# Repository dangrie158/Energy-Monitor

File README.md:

# Energy Monitor

A simple 6-channel  energy monitor for the whole house.
Uses 0-5V Current Transducers for current measureent and has a build-in voltage transformer for voltage measurement.
Brains are a Raspberry Pi Zero due to low cost and easy integration into the home WiFi and inclusion with MQTT or any other protocol to include the measurements in all kinds of home automation systems.

## Example Configuration

Channels 1, 2, 3 on L1, L2, L3 -> whole house consumption
Channels 4, 5, 6 on different room connections / devices

## Known Limitations

The Voltage is only measured on a single phase and thus only apperant power can be measured on the channels that connect to a different phase than the supply phase

## Licence

<p xmlns:dct="http://purl.org/dc/terms/" xmlns:vcard="http://www.w3.org/2001/vcard-rdf/3.0#">
  
</p>

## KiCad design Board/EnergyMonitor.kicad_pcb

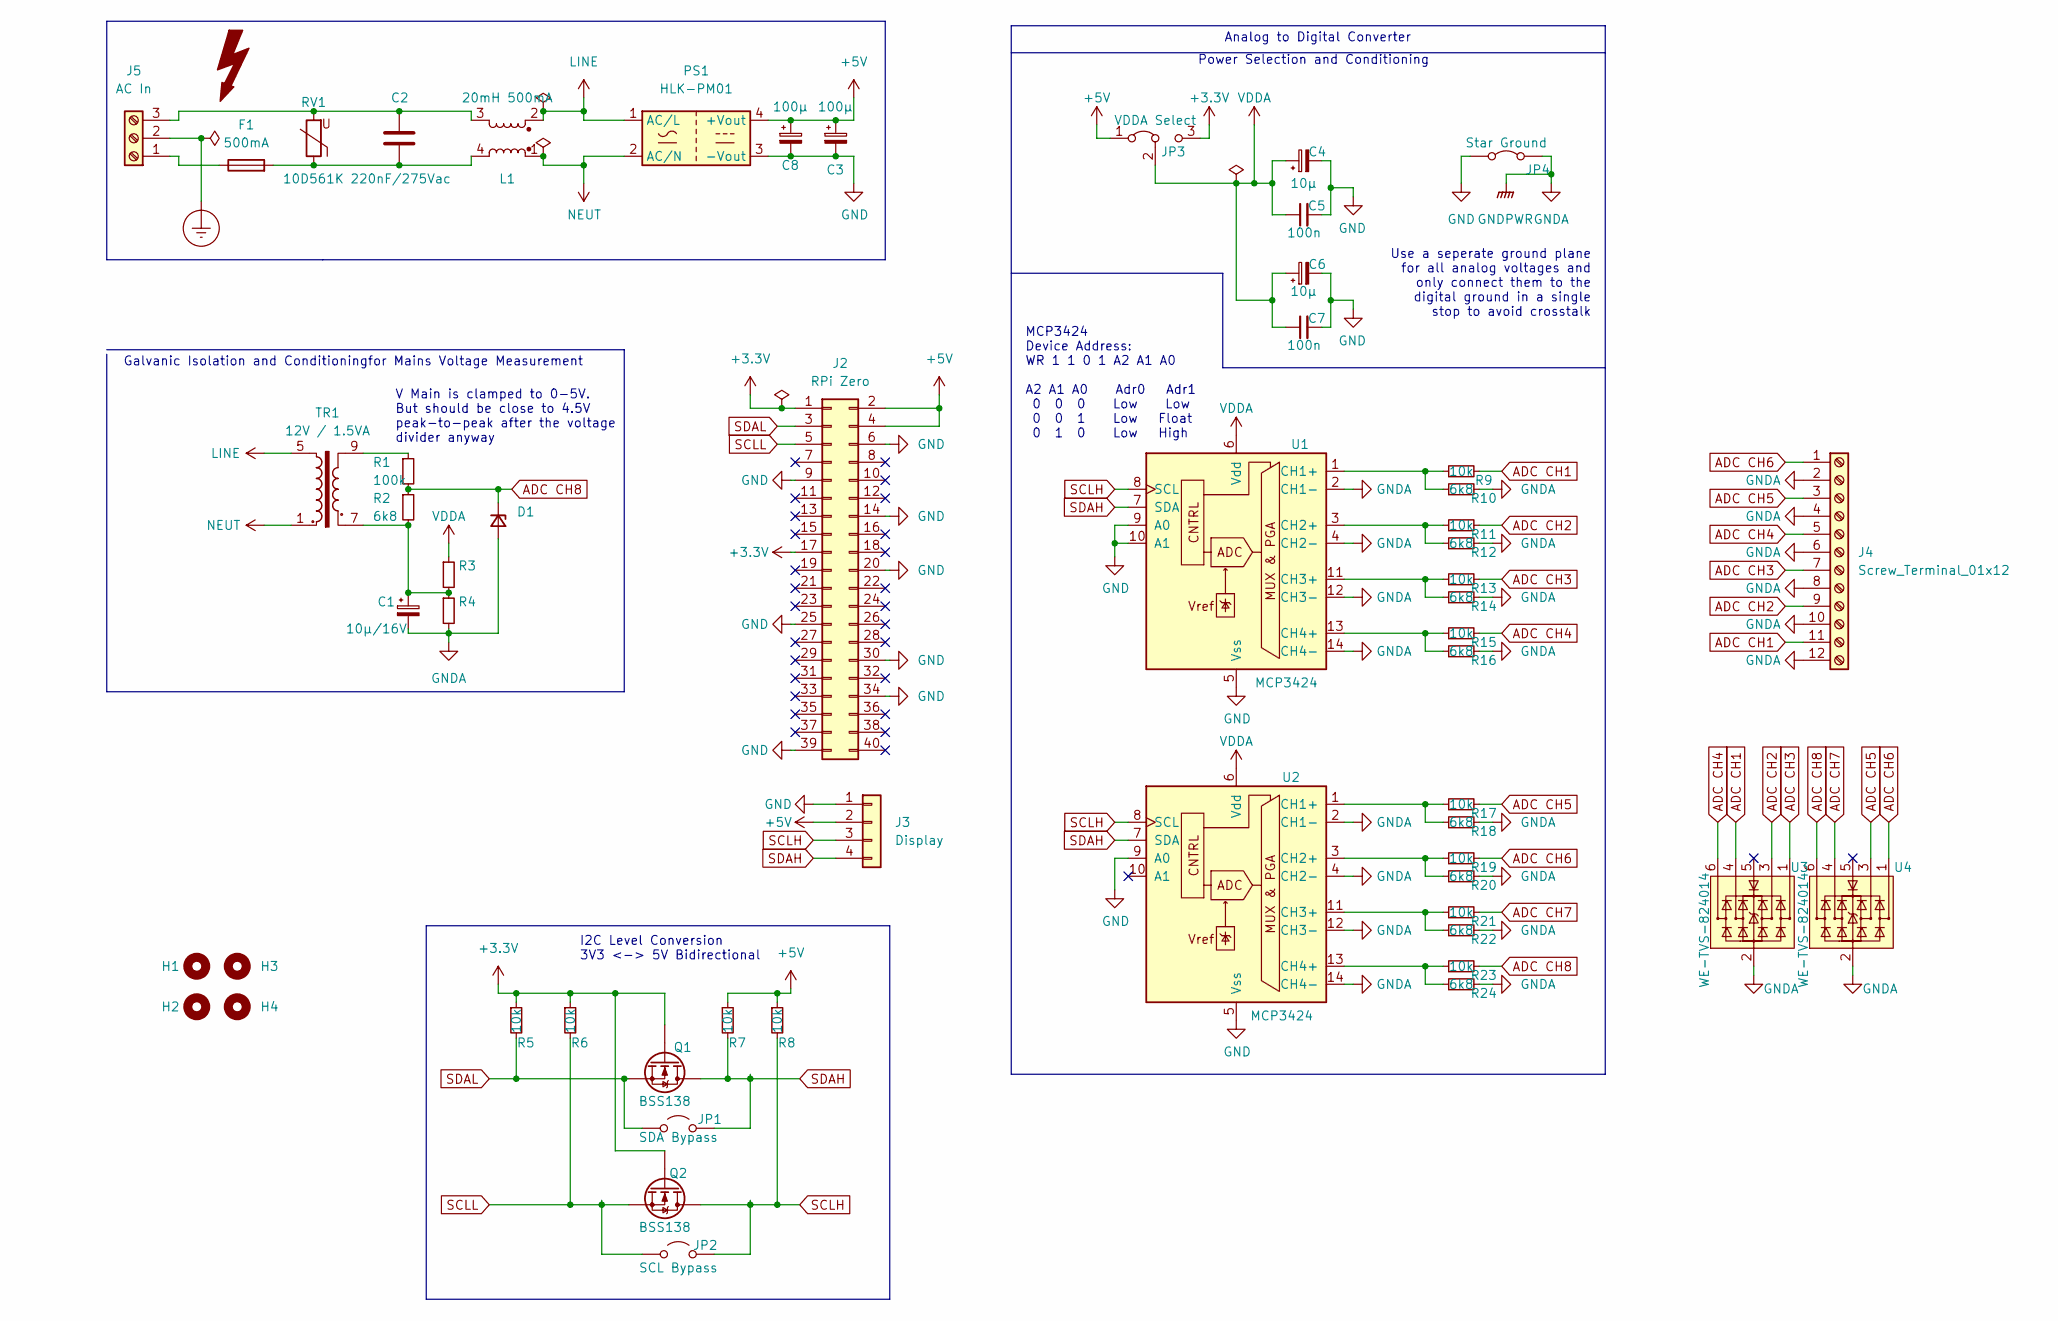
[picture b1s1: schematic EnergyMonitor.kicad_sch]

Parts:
C1: 10µ/16V; CP_EIA-3216-18_Kemet-A_Pad1.58x1.35mm_HandSolder
C2: 220nF/275Vac; C_Rect_L13.0mm_W6.0mm_P10.00mm_FKS3_FKP3_MKS4
C3, C8: 100µ; CP_Elec_5x5.4
C4, C6: 10µ; CP_EIA-3216-18_Kemet-A_Pad1.58x1.35mm_HandSolder
C5, C7: 100n; C_0603_1608Metric_Pad1.08x0.95mm_HandSolder
D1: D_MiniMELF_Handsoldering
F1: 500mA; Fuseholder_Cylinder-5x20mm_Schurter_0031_8201_Horizontal_Op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
H1, H2, H3, H4: MountingHole; MountingHole_2.7mm_M2.5_DIN965
J2: RPi Zero; Raspberry Pi Zero
J3: Display; JST_XH_B4B-XH-AM_1x04_P2.50mm_Vertical
J4: Screw_Terminal_01x12; TerminalBlock_Phoenix_PT-1,5-12-5.0-H_1x12_P5.00mm_Horizont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
J5: AC In; TerminalBlock_MetzConnect_Type175_RT02703HBLC_1x03_P7.50mm_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
JP1: SDA Bypass; SolderJumper-2_P1.3mm_Open_RoundedPad1.0x1.5mm
JP2: SCL Bypass; SolderJumper-2_P1.3mm_Open_RoundedPad1.0x1.5mm
JP3: VDDA Select; SolderJumper-3_P1.3mm_Bridged12_RoundedPad1.0x1.5mm
JP4: Star Ground; SolderJumper-2_P1.3mm_Bridged2Bar_RoundedPad1.0x1.5mm
L1: 20mH 500mA; UU9.8
PS1: HLK-PM01; Converter_ACDC_HiLink_HLK-PMxx
Q1, Q2: BSS138; SOT-23
R1: 100k; R_1206_3216Metric_Pad1.30x1.75mm_HandSolder
R2: 6k8; R_1206_3216Metric_Pad1.30x1.75mm_HandSolder
R3, R4: R_1206_3216Metric_Pad1.30x1.75mm_HandSolder
R5, R6, R7, R8, R9, R11, R13, R15, R17, R19, R21, R23: 10k; R_0603_1608Metric_Pad0.98x0.95mm_HandSolder
R10, R12, R14, R16, R18, R20, R22, R24: 6k8; R_0603_1608Metric_Pad0.98x0.95mm_HandSolder
RV1: 10D561K; RV_Disc_D12mm_W5.4mm_P7.5mm
TR1: 12V / 1.5VA; BV EL 30
U1, U2: MCP3424; SO-14_3.9x8.65mm_P1.27mm
U3, U4: WE-TVS-824014; SOT-23-6

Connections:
+3V3: J2.1, J2.17, JP3.3 (B), Q1.1 (G), Q2.1 (G), R5.1, R6.1
+5V: C3.1, C8.1, J2.2, J2.4, J3.2, JP3.1 (A), PS1.4 (+Vout), R7.1, R8.1
ADC CH1: J4.11, R9.2, U3.4
ADC CH2: J4.9, R11.2, U3.3
ADC CH3: J4.7, R13.2, U3.1
ADC CH4: J4.5, R15.2, U3.6
ADC CH5: J4.3, R17.2, U4.3
ADC CH6: J4.1, R19.2, U4.1
ADC CH7: R21.2, U4.4
ADC CH8: D1.1 (K), R1.2, R2.1, R23.2, U4.6
Earth_Protective: J5.2
GND: C3.2, C4.2, C5.2, C6.2, C7.2, C8.2, J2.6, J2.9, J2.14, J2.20, J2.25, J2.30, J2.34, J2.39, J3.1, JP4.1 (A), PS1.3 (-Vout), U1.5 (Vss), U1.9 (A0), U1.10 (A1), U2.5 (Vss), U2.9 (A0)
GNDA: C1.2, D1.2 (A), J4.2, J4.4, J4.6, J4.8, J4.10, J4.12, JP4.2 (B), R4.2, R10.2, R12.2, R14.2, R16.2, R18.2, R20.2, R22.2, R24.2, U1.2 (CH1-), U1.4 (CH2-), U1.12 (CH3-), U1.14 (CH4-), U2.2 (CH1-), U2.4 (CH2-), U2.12 (CH3-), U2.14 (CH4-), U3.2, U4.2
LINE: L1.2, PS1.1 (AC/L), TR1.5
NEUT: L1.1, PS1.2 (AC/N), TR1.1
unnamed: C1.1, R2.2, R3.2, R4.1, TR1.7
unnamed: C2.1, J5.3, L1.3, RV1.2
unnamed: C2.2, F1.2, L1.4, RV1.1
unnamed: F1.1, J5.1
unnamed: R1.1, TR1.9
unnamed: R9.1, R10.1, U1.1 (CH1+)
unnamed: R11.1, R12.1, U1.3 (CH2+)
unnamed: R13.1, R14.1, U1.11 (CH3+)
unnamed: R15.1, R16.1, U1.13 (CH4+)
unnamed: R17.1, R18.1, U2.1 (CH1+)
unnamed: R19.1, R20.1, U2.3 (CH2+)
unnamed: R21.1, R22.1, U2.11 (CH3+)
unnamed: R23.1, R24.1, U2.13 (CH4+)
SCLH: J3.3, JP2.2 (B), Q2.3 (D), R8.2, U1.8 (SCL), U2.8 (SCL)
SCLL: J2.5, JP2.1 (A), Q2.2 (S), R6.2
SDAH: J3.4, JP1.2 (B), Q1.3 (D), R7.2, U1.7 (SDA), U2.7 (SDA)
SDAL: J2.3, JP1.1 (A), Q1.2 (S), R5.2
VDDA: C4.1, C5.1, C6.1, C7.1, JP3.2 (C), R3.1, U1.6 (Vdd), U2.6 (Vdd)

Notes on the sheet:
Use a seperate ground plane for all analog voltages and only connect them to the digital ground in a single stop to avoid crosstalk
MCP3424 Device Address: WR 1 1 0 1 A2 A1 A0 A2 A1 A0 Adr0 Adr1 0 0 0 Low Low 0 0 1 Low Float 0 1 0 Low High
Galvanic Isolation and Conditioningfor Mains Voltage Measurement
V Main is clamped to 0-5V. But should be close to 4.5V peak-to-peak after the voltage divider anyway
Power Selection and Conditioning
Analog to Digital Converter
I2C Level Conversion 3V3 <-> 5V Bidirectional

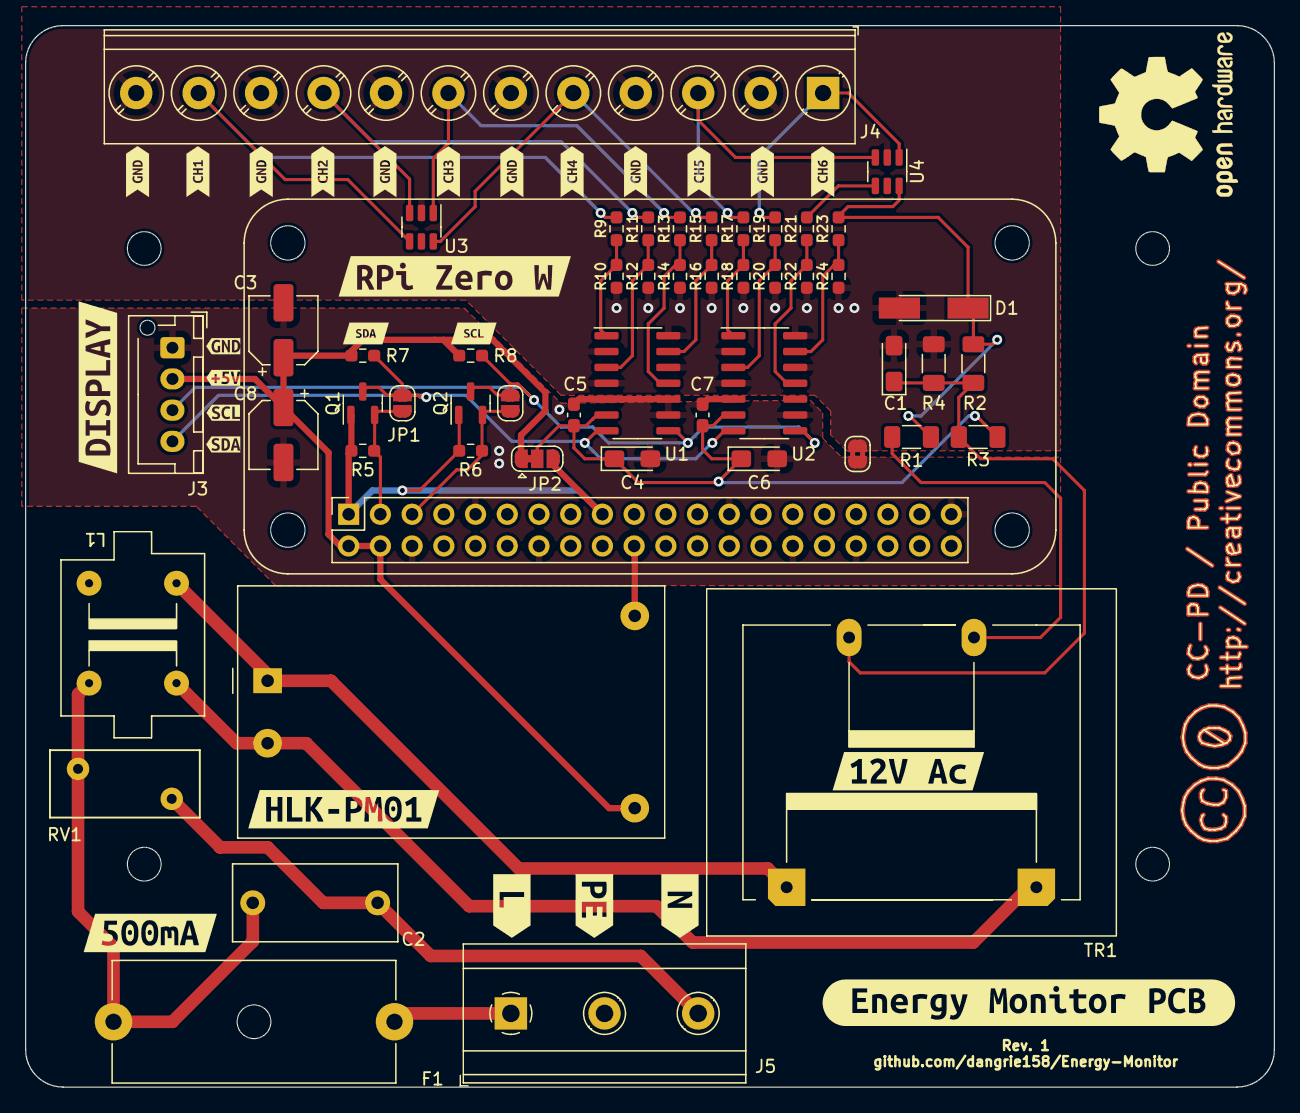
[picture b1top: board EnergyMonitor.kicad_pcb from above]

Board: 2 copper layers, 100.0 x 85.0 mm, 83 parts (0 on the bottom side), 32 nets.

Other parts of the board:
kibuzzard-6249A75F: G***; kibuzzard-6249A75F
kibuzzard-6249A77E: G***; kibuzzard-6249A77E
kibuzzard-6249A574: G***; kibuzzard-6249A574
kibuzzard-6249A738: G***; kibuzzard-6249A738
kibuzzard-6249A748: G***; kibuzzard-6249A748
kibuzzard-6249A773: G***; kibuzzard-6249A773
kibuzzard-6249A788: G***; kibuzzard-6249A788
kibuzzard-6249A794, kibuzzard-6249A794#2, kibuzzard-6249A794#3, kibuzzard-6249A794#4, kibuzzard-6249A794#5, kibuzzard-6249A794#6: G***; kibuzzard-6249A794
kibuzzard-6249ABCA: G***; kibuzzard-6249ABCA
kibuzzard-6249B42C: G***; kibuzzard-6249B42C
kibuzzard-6249B43B: G***; kibuzzard-6249B43B
kibuzzard-6249B420: G***; kibuzzard-6249B420
kibuzzard-6249B447: G***; kibuzzard-6249B447
kibuzzard-624990CE: G***; kibuzzard-624990CE
kibuzzard-624991A3: G***; kibuzzard-624991A3
kibuzzard-624991BE: G***; kibuzzard-624991BE
kibuzzard-624992C2: G***; kibuzzard-624992C2
kibuzzard-624992EE: G***; kibuzzard-624992EE
kibuzzard-6249901A: G***; kibuzzard-6249901A
kibuzzard-62499035: G***; kibuzzard-62499035
kibuzzard-62499525: G***; kibuzzard-62499525
kibuzzard-62499532: G***; kibuzzard-62499532

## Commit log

2022-04-02 initial board commit
2022-04-03 added creativ commons licence
2022-04-03 added attributions for 3d files
2022-04-03 fully routed pcb
2022-04-04 added macos ds_store files to gitignore
2022-04-04 resized PCB slightly for a better fit in the case
2022-04-04 added 3d step file of the board
2022-04-04 added gerbers from first pcb order
2022-04-05 added first draft of acquisition software with dummy adc
2022-04-06 added mocking capability for local development without hardware
2022-04-06 updated config.yaml to use corrext 1-based channel numbering
2022-04-06 fixed issue in sample aggregations
2022-04-06 config format cleanup
2022-04-06 implemented first types of statistic displays
2022-04-06 fixed compatability issue with python 3.9
2022-04-06 added systemd unit for service
2022-04-06 fixed mqtt message payload format to use proper telegraf format
2022-04-06 added new daily power history chart type
2022-04-06 improved font selection for readability
2022-04-06 added extra current channels to statistics and displays
2022-04-06 change extra small font to more legible non-monospaced variant
2022-04-07 added supervision of reader thread to automatically restart if the thread dies
2022-04-09 start mqtt client management loop to allow for automatic reconnections
2022-04-14 added first approximation for current measurement
2022-04-14 added live voltage display
2022-04-14 added moch channels for easy testing with partial hardware
2022-04-14 added configurable mqtt messages
2022-04-14 fixed unit error in total live power mqtt message
2022-04-14 added total daily power mqtt message
2022-04-14 switched to watts as base unit for power mqtt messages
2022-04-19 added updated configuration
2022-04-19 fixed some board layout issues after prototype assembly
2022-04-19 fixed configuration error
2022-04-23 refactored old adc module to respect signbit
2022-04-23 fixed error in 2s complement calculation
2022-04-23 do not populate pull up resistor on Vrms line
2022-04-23 fixed offset voltage for vrms measurment
2022-04-23 added configuration for extra channels
2022-04-23 adjusted configuration
2022-04-23 fixed masking error in 2s complement conversion
2022-04-23 adjusted configuration after fixing the conversion error
2022-04-23 updated board to match updated schematic

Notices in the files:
README.md:
CC0
